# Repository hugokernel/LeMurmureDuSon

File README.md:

LeMurmureDuSon
==============

Projet de l'équipe nº1 du Museolab 2013 : Le murmure du son

Développement d'un post'it vocal sous la forme d'un cube

Caractéristiques
----------------

- 1 message enregistrable par face
- 1 texture différente par face
- Chaque message est limité à 6 secondes
- Possibilité d'enregistrement d'un nouveau message sur chaque face
- Charge par induction
- Détection de la face exposée vers le haut (accéléromètre)
- Le cube est translucide
- 1 vibreur
- Éclairage par 1 ou plusieurs led RGB
- Sur batterie
- Réalisable en impression 3D

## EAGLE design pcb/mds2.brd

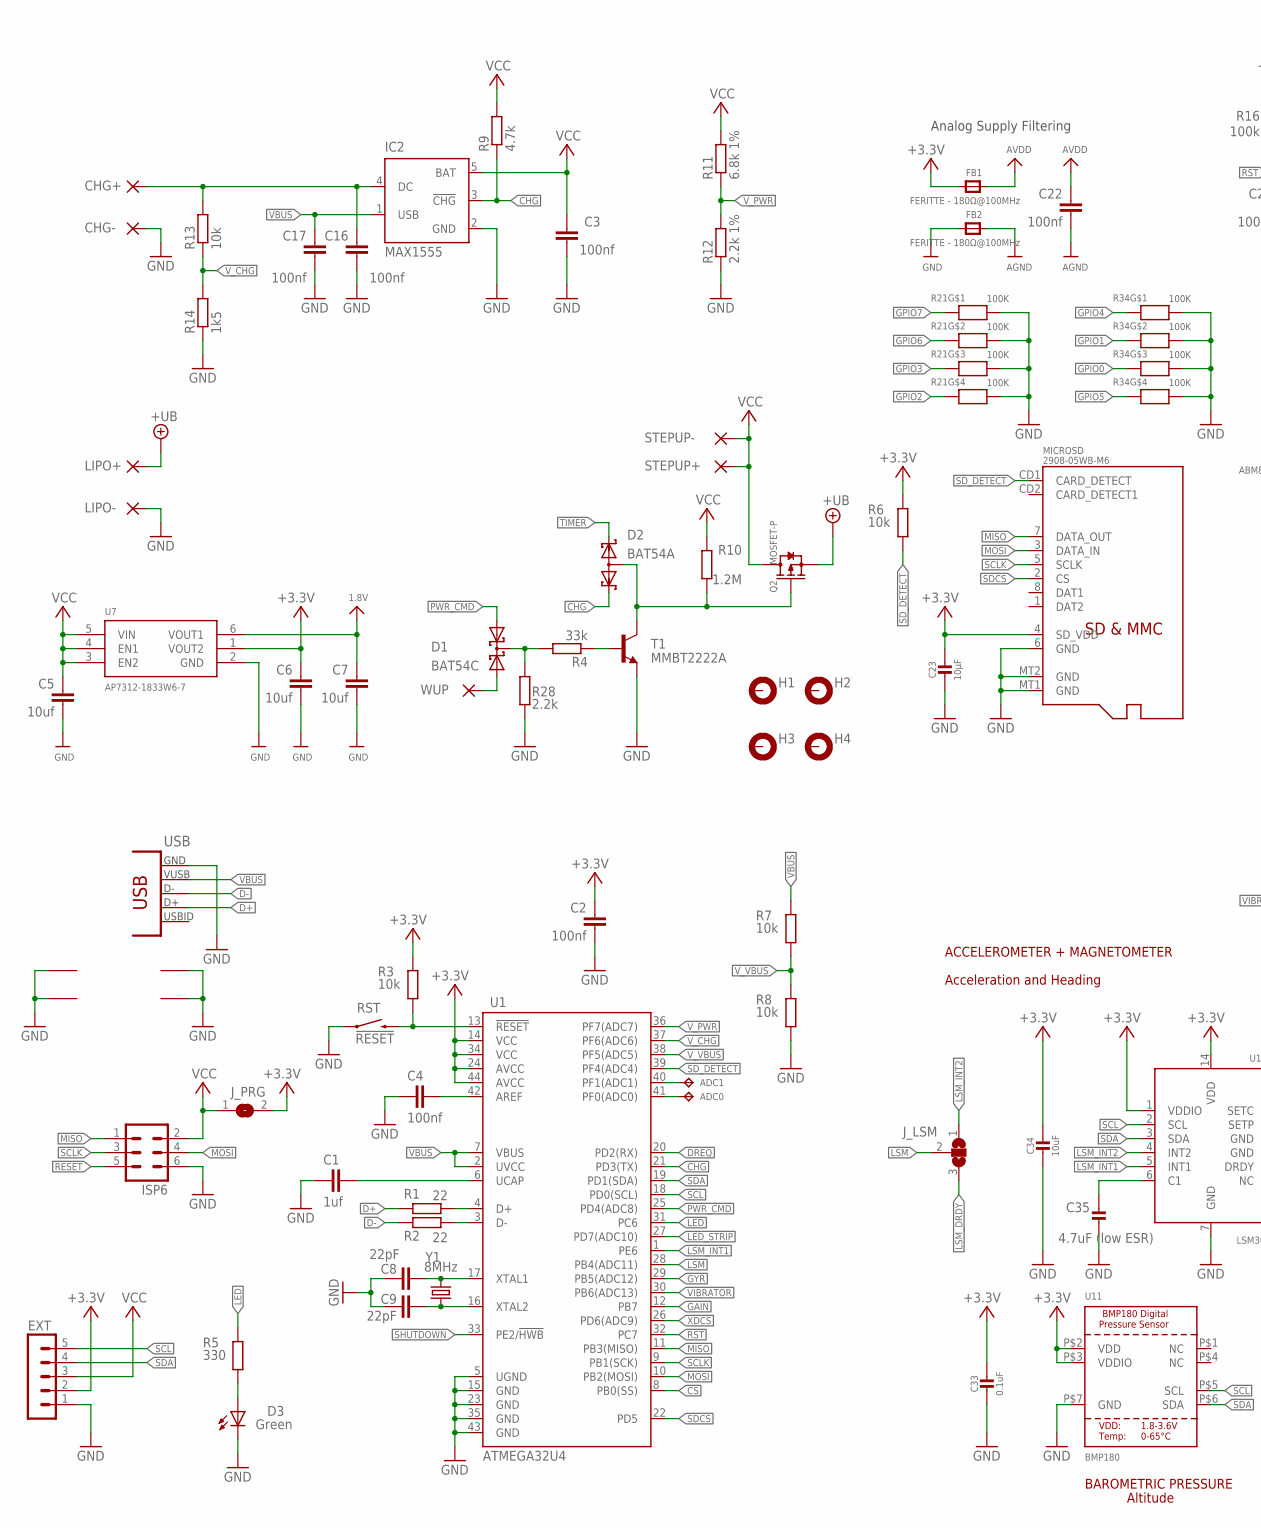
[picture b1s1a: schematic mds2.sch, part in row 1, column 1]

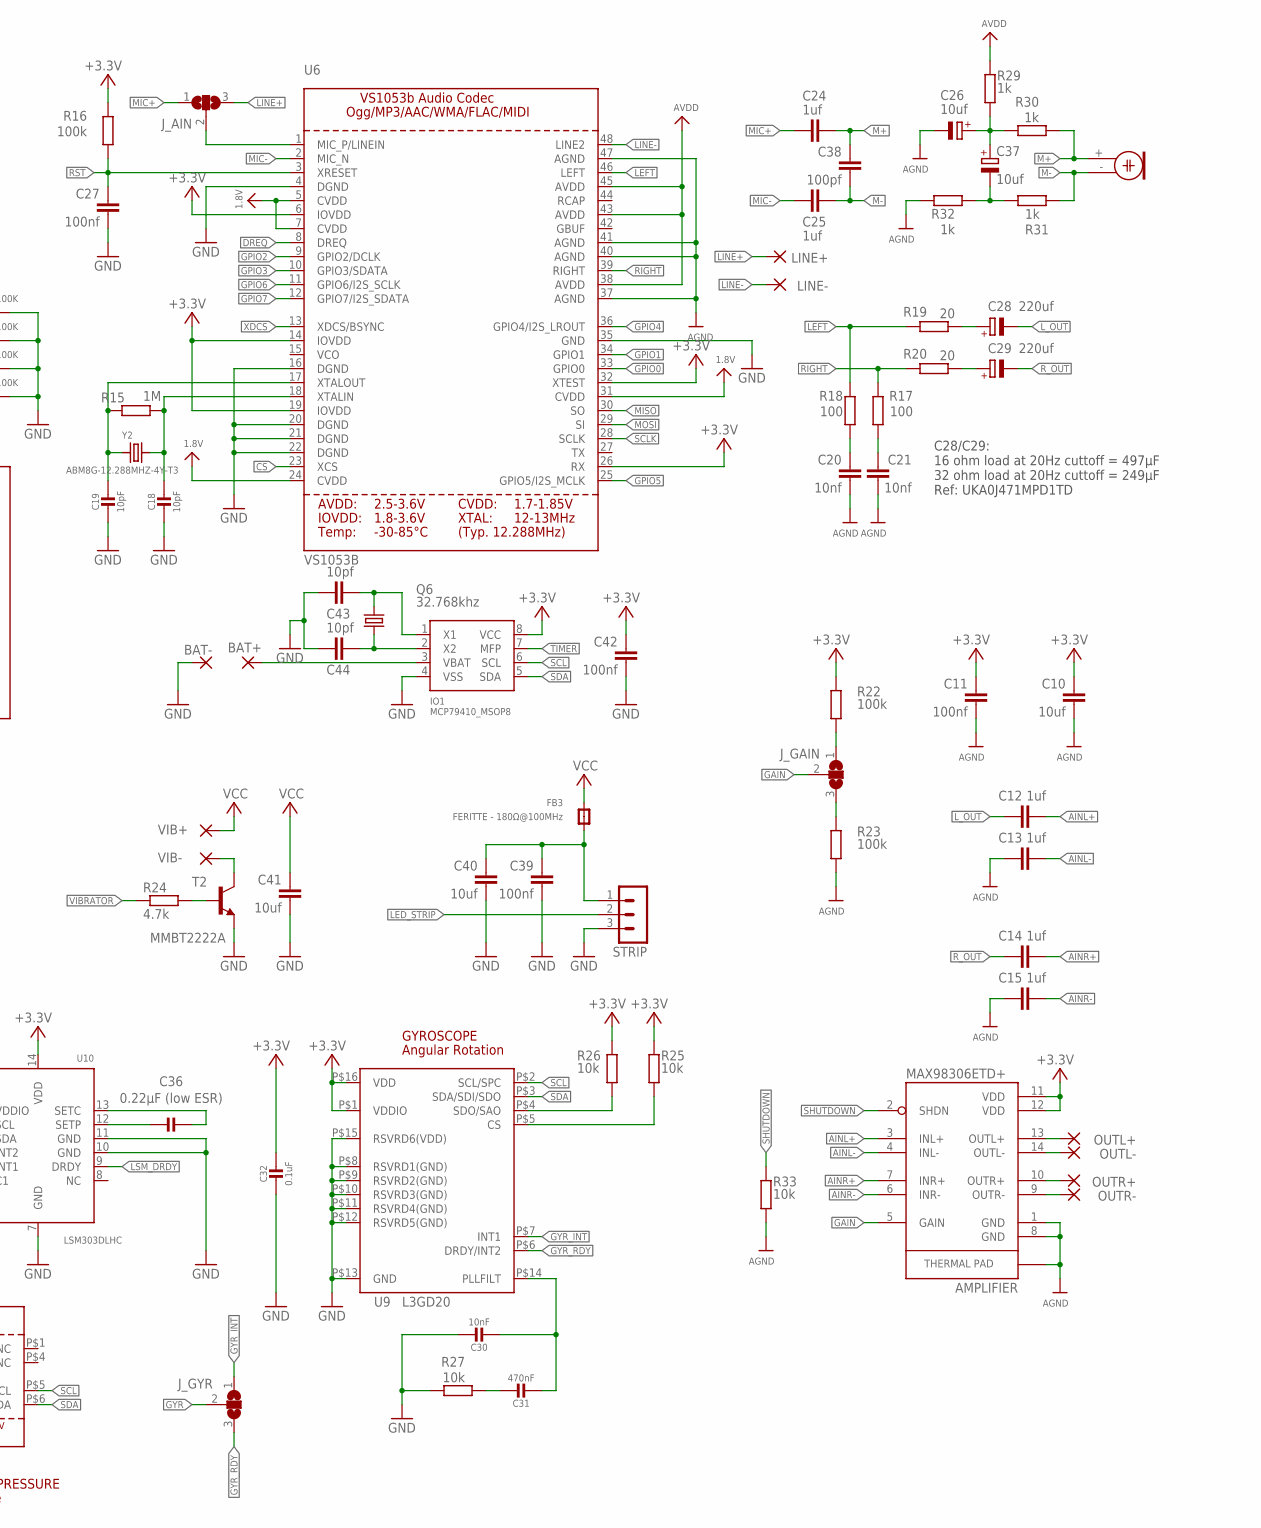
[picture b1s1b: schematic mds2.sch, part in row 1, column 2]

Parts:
ADC0, ADC1: TPB1,27; B1,27
AMPLIFIER: MAX98306ETD+; 14-TDFN
BAT+: 1,6/0,8
BAT-: 1,6/0,8
C1, C12, C13, C14, C15, C24, C25: 1uf; C0805
C2, C3, C4, C11, C16, C17, C22, C27, C39, C42: 100nf; C0805
C5, C6, C7, C10, C40, C41: 10uf; C0805
C8, C9: 22pF; 0402-CAP
C18, C19: 10pF; _0805MP
C20, C21: 10nf; C0805
C23: 10µF; _0805MP
C26, C37: 10uf; PANASONIC_C
C28, C29: 220uf; PANASONIC_D
C30: 10nF; _0805MP
C31: 470nF; _0805MP
C32, C33: 0.1uF; _0805MP
C34: 10uF; _0805MP
C35: 4.7uF (low ESR); _0805MP
C36: 0.22µF (low ESR); _0805MP
C38: 100pf; C0805
C43, C44: 10pf; C0805
CHG+: 2,15/1,0
CHG-: 2,15/1,0
D1: BAT54C; SOT23
D2: BAT54A; SOT23
D3: Green; LED-0603
EXT: MA05-1
FB1, FB2, FB3: FERITTE - 180Ω@100MHz; _0805MP
H1, H2, H3, H4: MOUNT-PAD-ROUND3.0; 3,0-PAD
IC2: MAX1555; SOT23-5L
IO1: MCP79410_MSOP8; MSOP8
ISP6: MA03-2
J_AIN: SJ2W; SJ_2
J_GAIN: SJ2W; SJ_2
J_GYR: SJ2W; SJ_2
J_LSM: SJ2W; SJ_2
J_PRG: SJ
LINE+: 1,6/0,8
LINE-: 1,6/0,8
LIPO+: 2,15/1,0
LIPO-: 2,15/1,0
MIC: ELECTRET_MICROPHON-TOM-1545P-R; TOM-1545P-R
MICROSD: 2908-05WB-M6; MICROSD
OUTL+: 2,15/1,0
OUTL-: 2,15/1,0
OUTR+: 2,15/1,0
OUTR-: 2,15/1,0
Q2: MOSFET-P; SOT23
Q6: 32.768khz; TC26H
R1, R2: 22; M0805
R3, R6, R7, R8, R13, R25, R26, R27, R33: 10k; M0805
R4: 33k; M0805
R5: 330; M0805
R9, R24: 4.7k; M0805
R10: 1.2M; M0805
R11: 6.8k 1%; M0805
R12: 2.2k 1%; M0805
R14: 1k5; M0805
R15: 1M; M0805
R16, R22, R23: 100k; M0805
R17, R18: 100; M0805
R19, R20: 20; M0805
R21, R34: 100K; RESPACK_4X0603
R28: 2.2k; M0805
R29, R30, R31, R32: 1k; M0805
RST: !RESET; TACTILE_SWITCH_SMD
STEPUP+: 2,15/1,0
STEPUP-: 2,15/1,0
STRIP: MA03-1
T1, T2: MMBT2222A; SOT23-BEC
U1: ATMEGA32U4; QFN-44-NOPAD
U6: VS1053B; LQFP48
U7: AP7312-1833W6-7; SOT23-6
U9: L3GD20; L3G4200D_LGA16L
U10: LSM303DLHC; LGA14
U11: BMP180; BMP180_EXTENDED
USB: CON-USB-F-MICRO-B; CONN_USB_MICRO-B
VIB+: 1,6/0,8
VIB-: 1,6/0,8
WUP: 1,6/0,8
Y1: 8MHz; CRYSTAL-SMD-5X3
Y2: ABM8G-12.288MHZ-4Y-T3; CRYSTAL_3.2X2.5

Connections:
1.8V: C7.2, U6.5 (CVDD), U6.7 (CVDD), U6.24 (CVDD), U6.31 (CVDD), U7.6 (VOUT1)
+3V3: AMPLIFIER.11 (VDD), AMPLIFIER.12 (VDD), C2.2, C6.2, C10.2, C11.2, C23.1, C32.1, C33.1, C34.1, C42.2, EXT.2, FB1.1, IO1.8 (VCC), J_PRG.2, MICROSD.4 (SD_VDD), R3.1, R6.1, R16.2, R22.2, R25.2, R26.2, U1.14 (VCC), U1.24 (AVCC), U1.34 (VCC), U1.44 (AVCC), U6.6 (IOVDD), U6.14 (IOVDD), U6.19 (IOVDD), U6.26 (RX), U6.32 (XTEST), U7.1 (VOUT2), U9.P$1 (VDDIO), U9.P$16 (VDD), U10.1 (VDDIO), U10.14 (VDD), U11.P$2 (VDD), U11.P$3 (VDDIO)
+UB: LIPO+.1, Q2.2 (S)
AGND: AMPLIFIER.1 (GND), AMPLIFIER.8 (GND), AMPLIFIER.15 (GND), C10.1, C11.1, C13.2, C15.2, C20.1, C21.1, C22.1, C26.-, FB2.2, R23.1, R32.1, R33.1, U6.37 (AGND), U6.40 (AGND), U6.41 (AGND), U6.47 (AGND)
AINL+: AMPLIFIER.3 (INL+), C12.1
AINL-: AMPLIFIER.4 (INL-), C13.1
AINR+: AMPLIFIER.7 (INR+), C14.1
AINR-: AMPLIFIER.6 (INR-), C15.1
AREF: C4.1, U1.42 (AREF)
AVDD: C22.2, FB1.2, R29.2, U6.38 (AVDD), U6.43 (AVDD), U6.45 (AVDD)
CHG: D2.2 (K2), IC2.3 (!CHG), R9.1, U1.21 (PD3(TX))
CS: U1.8 (PB0(SS)), U6.23 (XCS)
D+: R1.2, USB.P3 (D+)
D-: R2.2, USB.P2 (D-)
DREQ: U1.20 (PD2(RX)), U6.8 (DREQ)
GAIN: AMPLIFIER.5 (GAIN), J_GAIN.2, U1.12 (PB7)
GND: BAT-.1, C1.2, C2.1, C3.1, C4.2, C5.1, C6.1, C7.1, C8.2, C9.2, C16.1, C17.1, C18.2, C19.2, C23.2, C27.1, C30.1, C32.2, C33.2, C34.2, C35.2, C39.1, C40.1, C41.1, C42.1, C43.2, C44.2, CHG-.1, D3.C, EXT.1, FB2.1, IC2.2 (GND), IO1.4 (VSS), ISP6.6, LIPO-.1, MICROSD.6 (GND), MICROSD.MT1 (GND), MICROSD.MT2 (GND), R8.2, R12.1, R14.1, R21.5 (2), R21.6 (2), R21.7 (2), R21.8 (2), R27.1, R28.2, R34.5 (2), R34.6 (2), R34.7 (2), R34.8 (2), RST.1, STRIP.3, T1.E, T2.E, U1.5 (UGND), U1.15 (GND), U1.23 (GND), U1.35 (GND), U1.43 (GND), U6.4 (DGND), U6.16 (DGND), U6.20 (DGND), U6.21 (DGND), U6.22 (DGND), U6.35 (GND), U7.2 (GND), U9.P$8 (RSVRD1(GND)), U9.P$9 (RSVRD2(GND)), U9.P$10 (RSVRD3(GND)), U9.P$11 (RSVRD4(GND)), U9.P$12 (RSVRD5(GND)), U9.P$13 (GND), U9.P$15 (RSVRD6(VDD)), U10.7 (GND), U10.10 (GND), U10.11 (GND), U11.P$7 (GND), USB.BODY@1 (BODY), USB.BODY@2 (BODY)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
GPIO0: R34.3 (1), U6.33 (GPIO0)
GPIO1: R34.2 (1), U6.34 (GPIO1)
GPIO2: R21.4 (1), U6.9 (GPIO2/DCLK)
GPIO3: R21.3 (1), U6.10 (GPIO3/SDATA)
GPIO4: R34.1, U6.36 (GPIO4/I2S_LROUT)
GPIO5: R34.4 (1), U6.25 (GPIO5/I2S_MCLK)
GPIO6: R21.2 (1), U6.11 (GPIO6/I2S_SCLK)
GPIO7: R21.1, U6.12 (GPIO7/I2S_SDATA)
GYR: J_GYR.2, U1.29 (PB5(ADC12))
GYR_INT: J_GYR.1, U9.P$7 (INT1)
GYR_RDY: J_GYR.3, U9.P$6 (DRDY/INT2)
LED: R5.1, U1.31 (PC6)
LED_STRIP: STRIP.2, U1.27 (PD7(ADC10))
LEFT: R17.2, R19.2, U6.46 (LEFT)
LEFT_FILTERED: C28.+, R19.1
LINE+: J_AIN.3, LINE+.1
LINE-: LINE-.1, U6.48 (LINE2)
LSM: J_LSM.2, U1.28 (PB4(ADC11))
LSM_DRDY: J_LSM.3, U10.9 (DRDY)
LSM_INT1: U1.1 (PE6), U10.5 (INT1)
LSM_INT2: J_LSM.1, U10.4 (INT2)
L_OUT: C12.2, C28.-
M+: C24.1, C38.2, MIC.+ (1), R30.2
M-: C25.1, C38.1, MIC.- (2), R31.1
MIC+: C24.2, J_AIN.1
MIC-: C25.2, U6.2 (MIC_N)
MISO: ISP6.1, MICROSD.7 (DATA_OUT), U1.11 (PB3(MISO)), U6.30 (SO)
MOSI: ISP6.4, MICROSD.3 (DATA_IN), U1.10 (PB2(MOSI)), U6.29 (SI)
unnamed: C9.1, U1.16 (XTAL2), Y1.1
unnamed: R1.1, U1.4 (D+)
unnamed: C16.2, CHG+.1, IC2.4 (DC), R13.2
unnamed: C8.1, U1.17 (XTAL1), Y1.3 (2)
unnamed: C1.1, U1.6 (UCAP)
unnamed: C39.2, C40.2, FB3.1, STRIP.1
unnamed: R2.1, U1.3 (D-)
unnamed: D3.A, R5.2
unnamed: R4.1, T1.B
unnamed: D2.3 (AA), Q2.1 (G), R10.1, T1.C
unnamed: D1.3 (CC), R4.2, R28.1
unnamed: D1.2 (A2), WUP.1
unnamed: R24.2, T2.B
unnamed: T2.C, VIB-.1
unnamed: ADC1.TP, U1.40 (PF1(ADC1))
unnamed: J_AIN.2, U6.1 (MIC_P/LINEIN)
unnamed: AMPLIFIER.14 (OUTL-), OUTL-.1
unnamed: J_GAIN.1, R22.1
unnamed: AMPLIFIER.13 (OUTL+), OUTL+.1
unnamed: C37.-, R31.2, R32.2
unnamed: ADC0.TP, U1.41 (PF0(ADC0))
unnamed: C44.1, IO1.2 (X2), Q6.1
unnamed: C26.+, C37.+, R29.1, R30.1
unnamed: AMPLIFIER.10 (OUTR+), OUTR+.1
unnamed: AMPLIFIER.9 (OUTR-), OUTR-.1
unnamed: J_GAIN.3, R23.2
unnamed: C43.1, IO1.1 (X1), Q6.2
unnamed: C19.1, R15.2, U6.17 (XTALOUT), Y2.1
unnamed: C18.1, R15.1, U6.18 (XTALIN), Y2.2
unnamed: C20.2, R17.1
unnamed: C21.2, R18.1
unnamed: BAT+.1, IO1.3 (VBAT)
unnamed: R25.1, U9.P$5 (CS)
unnamed: R26.1, U9.P$4 (SDO/SAO)
unnamed: C31.1, R27.2
unnamed: C30.2, C31.2, U9.P$14 (PLLFILT)
unnamed: C35.1, U10.6 (C1)
unnamed: C36.1, U10.12 (SETP)
unnamed: C36.2, U10.13 (SETC)
PWR_CMD: D1.1 (A1), U1.25 (PD4(ADC8))
RESET: ISP6.5, R3.2, RST.3 (2), U1.13 (!RESET)
RIGHT: R18.2, R20.2, U6.39 (RIGHT)
RIGHT_FILTERED: C29.+, R20.1
RST: C27.2, R16.1, U1.32 (PC7), U6.3 (XRESET)
R_OUT: C14.2, C29.-
SCL: EXT.5, IO1.6 (SCL), U1.18 (PD0(SCL)), U9.P$2 (SCL/SPC), U10.2 (SCL), U11.P$5 (SCL)
SCLK: ISP6.3, MICROSD.5 (SCLK), U1.9 (PB1(SCK)), U6.28 (SCLK)
SDA: EXT.4, IO1.5 (SDA), U1.19 (PD1(SDA)), U9.P$3 (SDA/SDI/SDO), U10.3 (SDA), U11.P$6 (SDA)
SDCS: MICROSD.2 (CS), U1.22 (PD5)
SD_DETECT: MICROSD.CD1 (CARD_DETECT), R6.2, U1.39 (PF4(ADC4))
SHUTDOWN: AMPLIFIER.2 (SHDN), R33.2, U1.33 (PE2/!HWB)
TIMER: D2.1 (K1), IO1.7 (MFP)
VBUS: C17.2, IC2.1 (USB), R7.1, U1.2 (UVCC), U1.7 (VBUS), USB.P1 (VUSB)
VCC: C3.2, C5.2, C41.2, EXT.3, FB3.2, IC2.5 (BAT), ISP6.2, J_PRG.1, Q2.3 (D), R9.2, R10.2, R11.2, STEPUP+.1, STEPUP-.1, U7.3 (EN2), U7.4 (EN1), U7.5 (VIN), VIB+.1
VIBRATOR: R24.1, U1.30 (PB6(ADC13))
V_CHG: R13.1, R14.2, U1.37 (PF6(ADC6))
V_PWR: R11.1, R12.2, U1.36 (PF7(ADC7))
V_VBUS: R7.2, R8.1, U1.38 (PF5(ADC5))
XDCS: U1.26 (PD6(ADC9)), U6.13 (XDCS/BSYNC)

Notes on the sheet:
Analog Supply Filtering
C28/C29: 16 ohm load at 20Hz cuttoff = 497µF 32 ohm load at 20Hz cuttoff = 249µF Ref: UKA0J471MPD1TD
GYROSCOPE
Angular Rotation
ACCELEROMETER + MAGNETOMETER
Acceleration and Heading
BAROMETRIC PRESSURE
Altitude

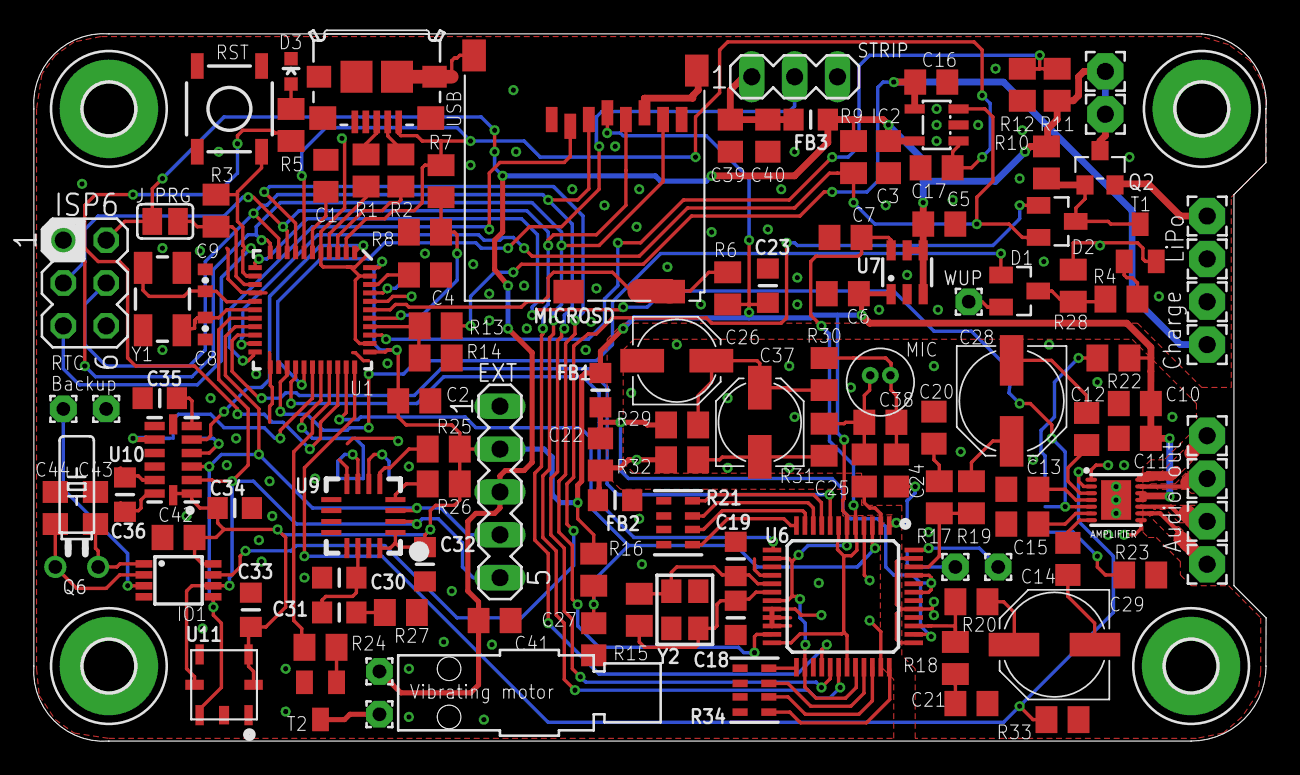
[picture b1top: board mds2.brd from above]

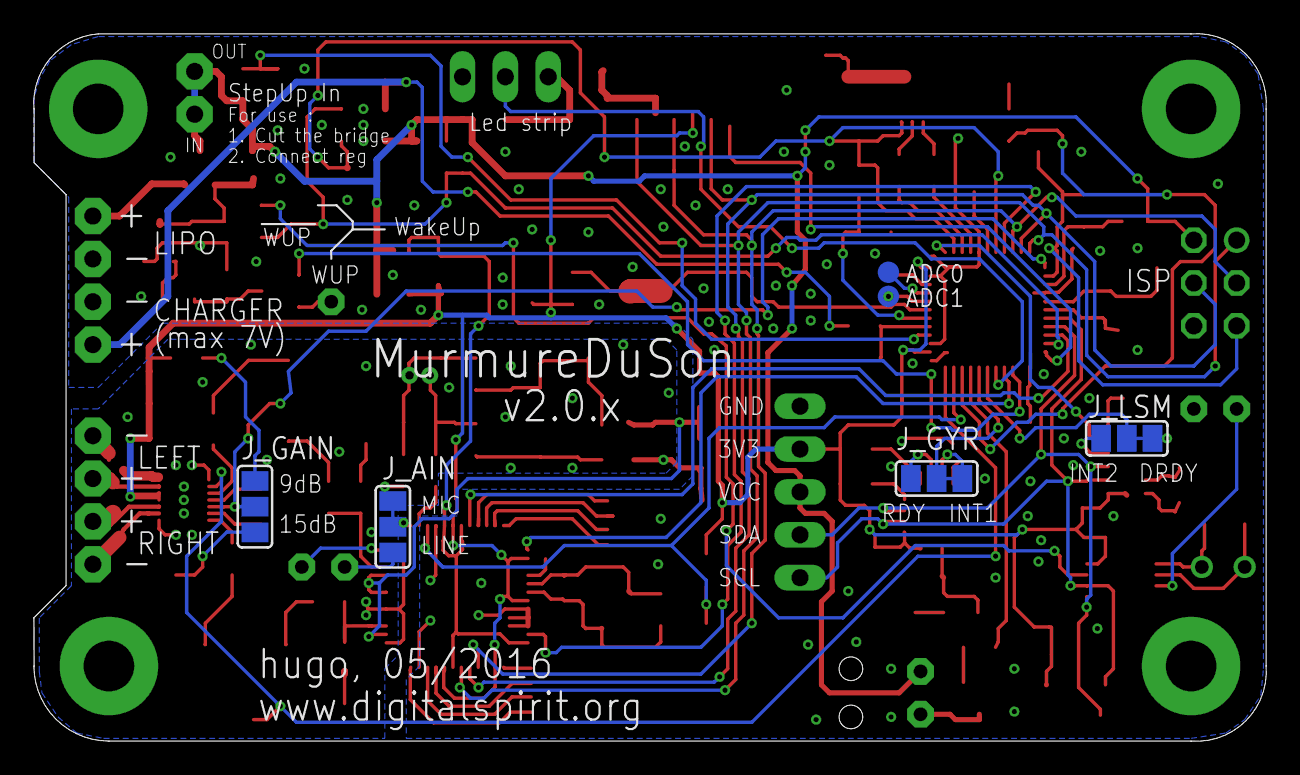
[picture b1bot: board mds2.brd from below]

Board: 2 copper layers, 73.0 x 41.9 mm, 134 parts (6 on the bottom side), 104 nets.

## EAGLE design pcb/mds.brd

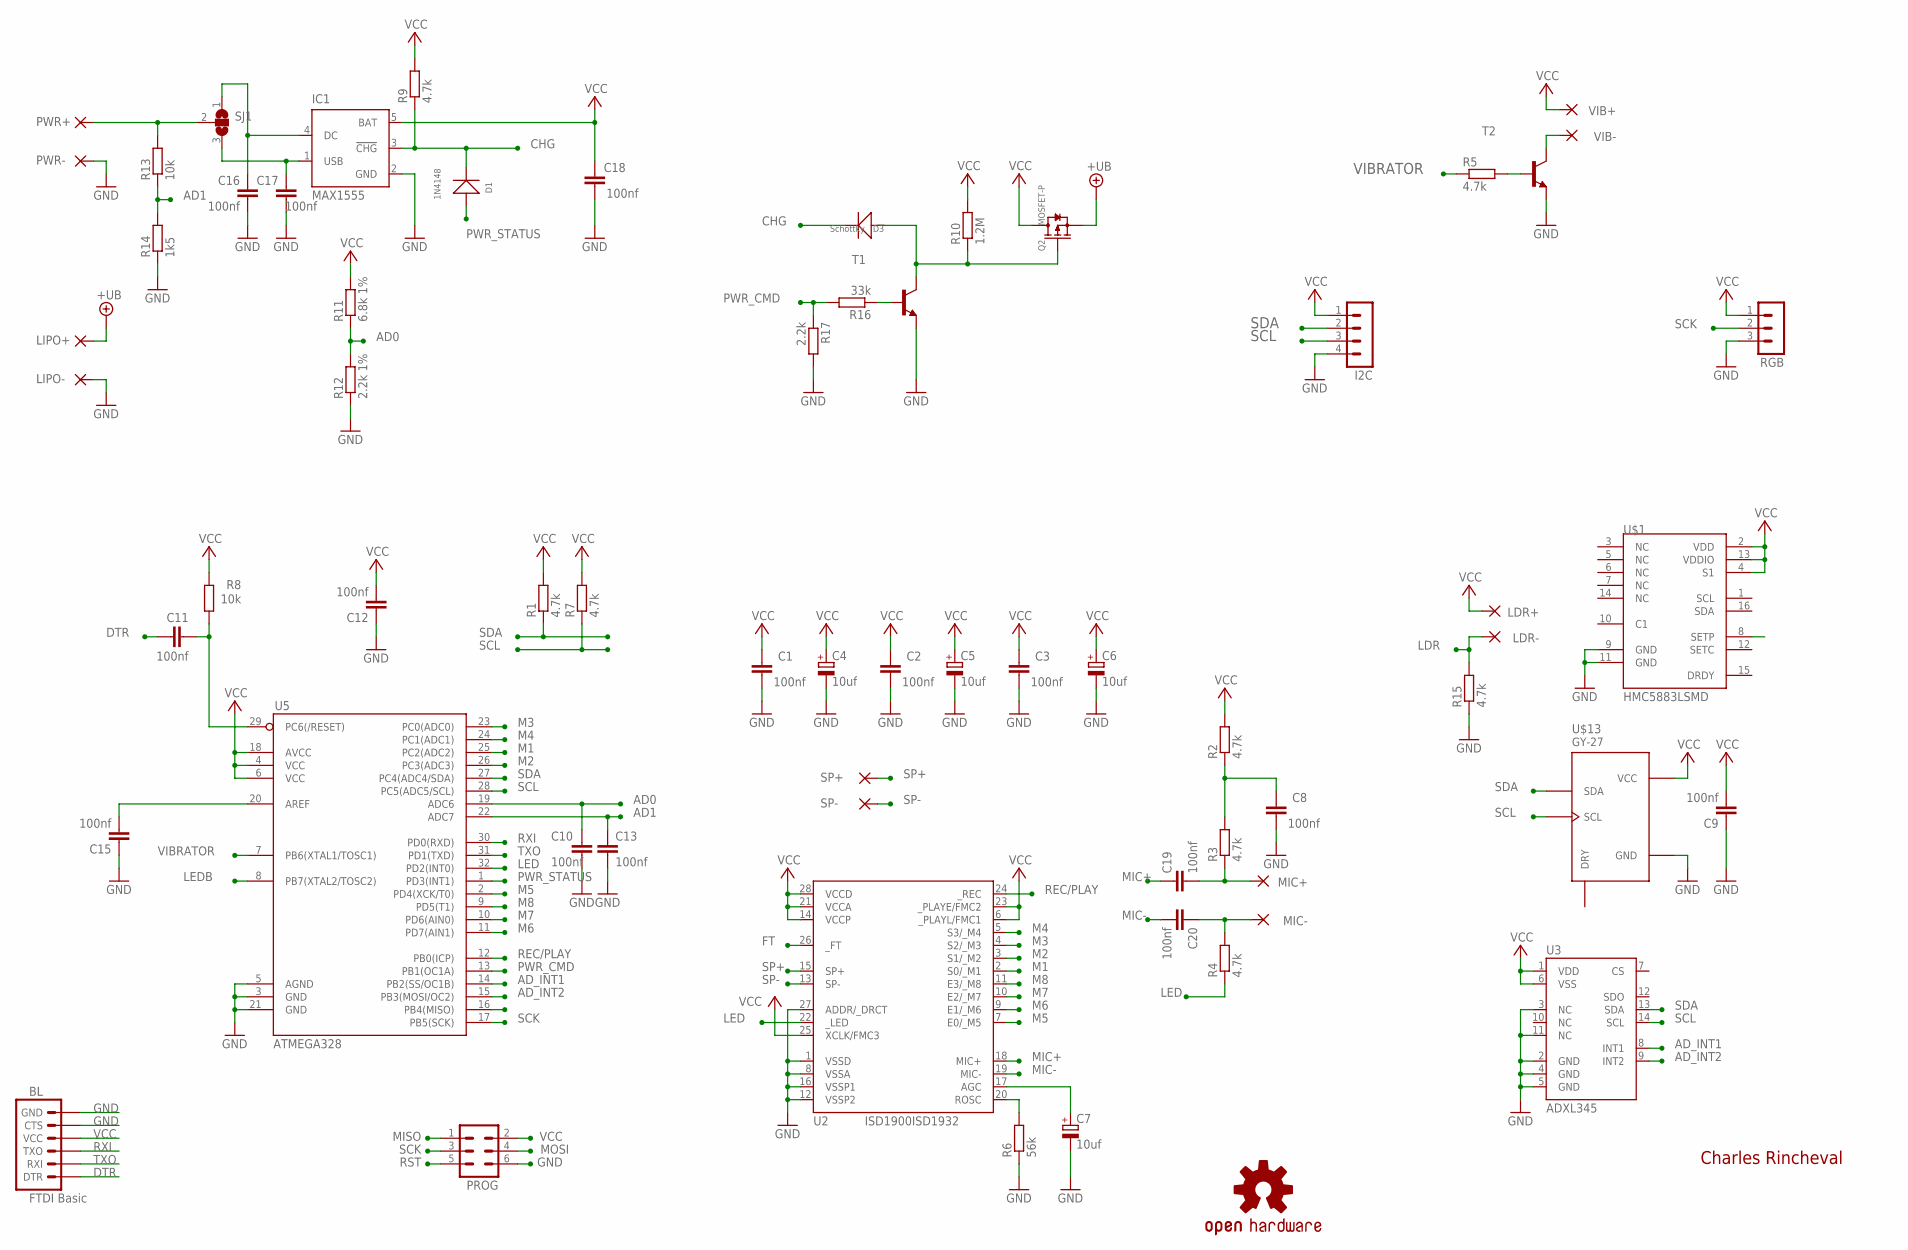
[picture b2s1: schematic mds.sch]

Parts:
BL: FTDI Basic; 1X06
C1, C2, C3, C8, C9, C10, C11, C12, C13, C15, C16, C17, C18, C19, C20: 100nf; C0805
C4, C5, C6, C7: 10uf; CT3528
D1: 1N4148; LL-34
D3: Schottky; LL-34
I2C: MA04-1
IC1: MAX1555; SOT23-5L
LDR+: 1,6/0,8
LDR-: 1,6/0,8
LIPO+: 1,6/0,8
LIPO-: 1,6/0,8
MIC+: 1,6/0,8
MIC-: 1,6/0,8
PROG: MA03-2
PWR+: 1,6/0,8
PWR-: 1,6/0,8
Q2: MOSFET-P; SOT23
R1, R2, R3, R4, R5, R7, R9, R15: 4.7k; M0805
R6: 56k; M0805
R8, R13: 10k; M0805
R10: 1.2M; M0805
R11: 6.8k 1%; M0805
R12: 2.2k 1%; M0805
R14: 1k5; M0805
R16: 33k; M0805
R17: 2.2k; M0805
RGB: MA03-1
SJ1: SJ2W; SJ_2
SP+: 1,6/0,8
SP-: 1,6/0,8
T1, T2: MMBT2222ALT1-NPN-SOT23-BEC; SOT23-BEC
U2: ISD1900ISD1932; SO-28W
U3: ADXL345; LGA14
U5: ATMEGA328; TQFP32-08
U$1: HMC5883LSMD; 16LPCC
U$13: GY-27
U$14: OSHW-LOGOS; OSHW-LOGO-S
VIB+: 1,6/0,8
VIB-: 1,6/0,8

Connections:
+UB: LIPO+.1, Q2.2 (S)
AD0: C10.1, R11.1, R12.2, U5.19 (ADC6)
AD1: C13.1, R13.1, R14.2, U5.22 (ADC7)
AD_INT1: U3.8 (INT1), U5.14 (PB2(SS/OC1B))
AD_INT2: U3.9 (INT2), U5.15 (PB3(MOSI/OC2))
AGC: C7.+, U2.17 (AGC)
AREF: C15.2, U5.20 (AREF)
CHG: D1.C (-), D3.C (-), IC1.3 (!CHG), R9.1
DTR: BL.1 (DTR), C11.1
FT: U2.26 (_FT)
GND: BL.5 (CTS), BL.6 (GND), C1.1, C2.1, C3.1, C4.-, C5.-, C6.-, C7.-, C8.1, C9.1, C10.2, C12.1, C13.2, C15.1, C16.1, C17.1, C18.1, I2C.4, IC1.2 (GND), LIPO-.1, PROG.6, PWR-.1, R6.1, R12.1, R14.1, R15.1, R17.2, RGB.3, T1.E, T2.E, U2.1 (VSSD), U2.8 (VSSA), U2.12 (VSSP2), U2.16 (VSSP1), U2.27 (ADDR/_DRCT), U3.2 (GND), U3.3 (NC), U3.4 (GND), U3.5 (GND), U3.11 (NC), U5.3 (GND), U5.5 (AGND), U5.21 (GND), U$1.9 (GND), U$1.11 (GND), U$13.GND
LDR: LDR-.1, R15.2
LED: R4.1, U2.22 (_LED), U5.32 (PD2(INT0))
LEDB: U5.8 (PB7(XTAL2/TOSC2))
M1: U2.2 (S0/_M1), U5.25 (PC2(ADC2))
M2: U2.3 (S1/_M2), U5.26 (PC3(ADC3))
M3: U2.4 (S2/_M3), U5.23 (PC0(ADC0))
M4: U2.5 (S3/_M4), U5.24 (PC1(ADC1))
M5: U2.7 (E0/_M5), U5.2 (PD4(XCK/T0))
M6: U2.9 (E1/_M6), U5.11 (PD7(AIN1))
M7: U2.10 (E2/_M7), U5.10 (PD6(AIN0))
M8: U2.11 (E3/_M8), U5.9 (PD5(T1))
MIC+: C19.1, U2.18 (MIC+)
MIC-: C20.2, U2.19 (MIC-)
MISO: PROG.1
MOSI: PROG.4
unnamed: R6.2, U2.20 (ROSC)
unnamed: C19.2, MIC+.1, R3.1
unnamed: C20.1, MIC-.1, R4.2
unnamed: R16.1, T1.B
unnamed: R5.2, T2.B
unnamed: C8.2, R2.1, R3.2
unnamed: T2.C, VIB-.1
unnamed: PWR+.1, R13.2, SJ1.2
unnamed: Q2.1 (G), R10.1, T1.C
unnamed: C17.2, IC1.1 (USB), SJ1.3
unnamed: C16.2, IC1.4 (DC), SJ1.1
PWR_CMD: R16.2, R17.1, U5.13 (PB1(OC1A))
PWR_STATUS: D1.A (+), U5.1 (PD3(INT1))
REC/PLAY: U2.24 (_REC), U5.12 (PB0(ICP))
RST: C11.2, PROG.5, R8.1, U5.29 (PC6(/RESET))
RXI: BL.3 (TXO), U5.30 (PD0(RXD))
SCK: PROG.3, RGB.2, U5.17 (PB5(SCK))
SCL: I2C.3, R7.1, U3.14 (SCL), U5.28 (PC5(ADC5/SCL)), U$13.SCL
SDA: I2C.2, R1.1, U3.13 (SDA), U5.27 (PC4(ADC4/SDA)), U$13.SDA
SP+: SP+.1, U2.15 (SP+)
SP-: SP-.1, U2.13 (SP-)
TXO: BL.2 (RXI), U5.31 (PD1(TXD))
VCC: BL.4 (VCC), C1.2, C2.2, C3.2, C4.+, C5.+, C6.+, C9.2, C12.2, C18.2, I2C.1, IC1.5 (BAT), LDR+.1, PROG.2, Q2.3 (D), R1.2, R2.2, R7.2, R8.2, R9.2, R10.2, R11.2, RGB.1, U2.6 (_PLAYL/FMC1), U2.14 (VCCP), U2.21 (VCCA), U2.23 (_PLAYE/FMC2), U2.25 (XCLK/FMC3), U2.28 (VCCD), U3.1 (VDD), U3.6 (VSS), U5.4 (VCC), U5.6 (VCC), U5.18 (AVCC), U$1.2 (VDD), U$1.4 (S1), U$1.13 (VDDIO), U$13.VCC, VIB+.1
VIBRATOR: R5.1, U5.7 (PB6(XTAL1/TOSC1))

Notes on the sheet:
Charles Rincheval

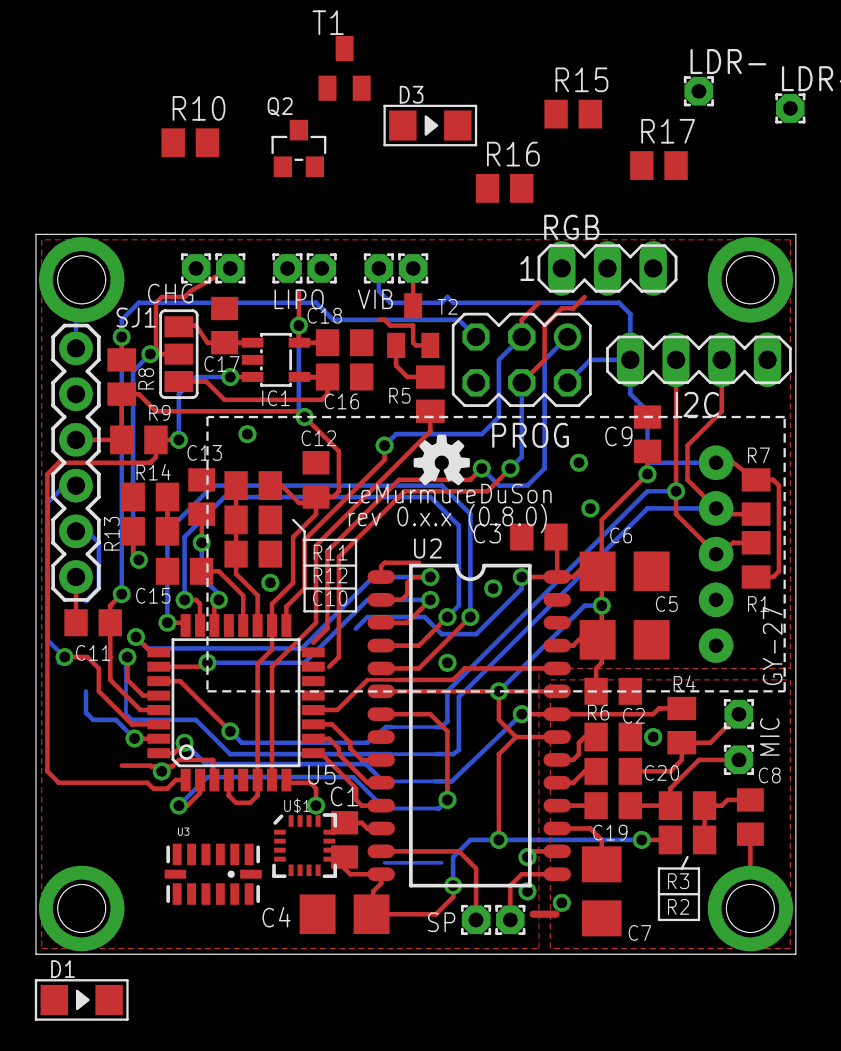
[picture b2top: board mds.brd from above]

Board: 2 copper layers, 42.2 x 40.0 mm, 65 parts (0 on the bottom side), 46 nets.

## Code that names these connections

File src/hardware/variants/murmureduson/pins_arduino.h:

/*
  pins_arduino.h - Pin definition functions for Arduino
  Part of Arduino - http://www.arduino.cc/

  Copyright (c) 2007 David A. Mellis

  This library is free software; you can redistribute it and/or
  modify it under the terms of the GNU Lesser General Public
  License as published by the Free Software Foundation; either
  version 2.1 of the License, or (at your option) any later version.

  This library is distributed in the hope that it will be useful,
  but WITHOUT ANY WARRANTY; without even the implied warranty of
  MERCHANTABILITY or FITNESS FOR A PARTICULAR PURPOSE.  See the GNU
  Lesser General Public License for more details.

  You should have received a copy of the GNU Lesser General
  Public License along with this library; if not, write to the
  Free Software Foundation, Inc., 59 Temple Place, Suite 330,
  Boston, MA  02111-1307  USA

  $Id: wiring.h 249 2007-02-03 16:52:51Z mellis $
*/

#ifndef Pins_Arduino_h
#define Pins_Arduino_h

#include <avr/pgmspace.h>

// Workaround for wrong definitions in "iom32u4.h".
// This should be fixed in the AVR toolchain.
#undef UHCON
#undef UHINT
#undef UHIEN
#undef UHADDR
#undef UHFNUM
#undef UHFNUML
#undef UHFNUMH
#undef UHFLEN
#undef UPINRQX
#undef UPINTX
#undef UPNUM
#undef UPRST
#undef UPCONX
#undef UPCFG0X
#undef UPCFG1X
#undef UPSTAX
#undef UPCFG2X
#undef UPIENX
#undef UPDATX
#undef TCCR2A
#undef WGM20
#undef WGM21
#undef COM2B0
#undef COM2B1
#undef COM2A0
#undef COM2A1
#undef TCCR2B
#undef CS20
#undef CS21
#undef CS22
#undef WGM22
#undef FOC2B
#undef FOC2A
#undef TCNT2
#undef TCNT2_0
#undef TCNT2_1
#undef TCNT2_2
#undef TCNT2_3
#undef TCNT2_4
#undef TCNT2_5
#undef TCNT2_6
#undef TCNT2_7
#undef OCR2A
#undef OCR2_0
#undef OCR2_1
#undef OCR2_2
#undef OCR2_3
#undef OCR2_4
#undef OCR2_5
#undef OCR2_6
#undef OCR2_7
#undef OCR2B
#undef OCR2_0
#undef OCR2_1
#undef OCR2_2
#undef OCR2_3
#undef OCR2_4
#undef OCR2_5
#undef OCR2_6
#undef OCR2_7

#define NUM_DIGITAL_PINS  30
#define NUM_ANALOG_INPUTS 12

#define TX_RX_LED_INIT	; //DDRD |= (1<<5), DDRB |= (1<<0)
#define TXLED0			; //PORTD |= (1<<5)
#define TXLED1			; //PORTD &= ~(1<<5)
#define RXLED0			; //PORTB |= (1<<0)
#define RXLED1			; //PORTB &= ~(1<<0)

static const uint8_t SDA = 2;
static const uint8_t SCL = 3;

// Map SPI port to 'new' pins D14..D17
static const uint8_t SS   = 17;
static const uint8_t MOSI = 16;
static const uint8_t MISO = 14;
static const uint8_t SCK  = 15;

// Mapping of analog pins as digital I/O
// A6-A11 share with digital pins
static const uint8_t A0 = 18;
static const uint8_t A1 = 19;
static const uint8_t A2 = 20;
static const uint8_t A3 = 21;
static const uint8_t A4 = 22;
static const uint8_t A5 = 23;
static const uint8_t A6 = 24;	// D4
static const uint8_t A7 = 25;	// D6
static const uint8_t A8 = 26;	// D8
static const uint8_t A9 = 27;	// D9
static const uint8_t A10 = 28;	// D10
static const uint8_t A11 = 29;	// D12

#define digitalPinToPCICR(p)    ((((p) >= 8 && (p) <= 11) || ((p) >= 14 && (p) <= 17) || ((p) >= A8 && (p) <= A10)) ? (&PCICR) : ((uint8_t *)0))
#define digitalPinToPCICRbit(p) 0
#define digitalPinToPCMSK(p)    ((((p) >= 8 && (p) <= 11) || ((p) >= 14 && (p) <= 17) || ((p) >= A8 && (p) <= A10)) ? (&PCMSK0) : ((uint8_t *)0))
#define digitalPinToPCMSKbit(p) ( ((p) >= 8 && (p) <= 11) ? (p) - 4 : ((p) == 14 ? 3 : ((p) == 15 ? 1 : ((p) == 16 ? 2 : ((p) == 17 ? 0 : (p - A8 + 4))))))

//	__AVR_ATmega32U4__ has an unusual mapping of pins to channels
extern const uint8_t PROGMEM analog_pin_to_channel_PGM[];
#define analogPinToChannel(P)  ( pgm_read_byte( analog_pin_to_channel_PGM + (P) ) )

#ifdef ARDUINO_MAIN

// On the Arduino board, digital pins are also used
// for the analog output (software PWM).  Analog input
// pins are a separate set.

// ATMEL ATMEGA32U4 / ARDUINO LEONARDO
//
// D0				PD2					RXD1/INT2
// D1				PD3					TXD1/INT3
// D2				PD1		SDA			SDA/INT1
// D3#				PD0		PWM8/SCL	OC0B/SCL/INT0
// D4		A6		PD4					ADC8
// D5#				PC6		???			OC3A/#OC4A
// D6#		A7		PD7		FastPWM		#OC4D/ADC10
// D7				PE6					INT6/AIN0
//
// D8		A8		PB4					ADC11/PCINT4
// D9#		A9		PB5		PWM16		OC1A/#OC4B/ADC12/PCINT5
// D10#		A10		PB6		PWM16		OC1B/0c4B/ADC13/PCINT6
// D11#				PB7		PWM8/16		0C0A/OC1C/#RTS/PCINT7
// D12		A11		PD6					T1/#OC4D/ADC9
// D13#				PC7		PWM10		CLK0/OC4A
//
// A0		D18		PF7					ADC7
// A1		D19		PF6					ADC6
// A2		D20 	PF5					ADC5
// A3		D21 	PF4					ADC4
// A4		D22		PF1					ADC1
// A5		D23 	PF0					ADC0
//
// New pins D14..D17 to map SPI port to digital pins
//
// MISO		D14		PB3					MISO,PCINT3
// SCK		D15		PB1					SCK,PCINT1
// MOSI		D16		PB2					MOSI,PCINT2
// SS		D17		PB0					RXLED,SS/PCINT0
//
// TXLED			PD5
// RXLED		    PB0
// HWB				PE2					HWB

// these arrays map port names (e.g. port B) to the
// appropriate addresses for various functions (e.g. reading
// and writing)
const uint16_t PROGMEM port_to_mode_PGM[] = {
	NOT_A_PORT,
	NOT_A_PORT,
	(uint16_t) &DDRB,
	(uint16_t) &DDRC,
	(uint16_t) &DDRD,
	(uint16_t) &DDRE,
	(uint16_t) &DDRF,
};

const uint16_t PROGMEM port_to_output_PGM[] = {
	NOT_A_PORT,
	NOT_A_PORT,
	(uint16_t) &PORTB,
	(uint16_t) &PORTC,
	(uint16_t) &PORTD,
	(uint16_t) &PORTE,
	(uint16_t) &PORTF,
};

const uint16_t PROGMEM port_to_input_PGM[] = {
	NOT_A_PORT,
	NOT_A_PORT,
	(uint16_t) &PINB,
	(uint16_t) &PINC,
	(uint16_t) &PIND,
	(uint16_t) &PINE,
	(uint16_t) &PINF,
};

const uint8_t PROGMEM digital_pin_to_port_PGM[] = {
	PD, // D0 - PD2
	PD,	// D1 - PD3
	PD, // D2 - PD1
	PD,	// D3 - PD0
	PD,	// D4 - PD4
	PC, // D5 - PC6
	PD, // D6 - PD7
	PE, // D7 - PE6
	
	PB, // D8 - PB4
	PB,	// D9 - PB5
	PB, // D10 - PB6
	PB,	// D11 - PB7
	PD, // D12 - PD6
	PC, // D13 - PC7
	
	PB,	// D14 - MISO - PB3
	PB,	// D15 - SCK - PB1
	PB,	// D16 - MOSI - PB2
	PB,	// D17 - SS - PB0
	
	PF,	// D18 - A0 - PF7
	PF, // D19 - A1 - PF6
	PF, // D20 - A2 - PF5
	PF, // D21 - A3 - PF4
	PF, // D22 - A4 - PF1
	PF, // D23 - A5 - PF0
	
	PD, // D24 / D4 - A6 - PD4
	PD, // D25 / D6 - A7 - PD7
	PB, // D26 / D8 - A8 - PB4
	PB, // D27 / D9 - A9 - PB5
	PB, // D28 / D10 - A10 - PB6
	PD, // D29 / D12 - A11 - PD6
};

const uint8_t PROGMEM digital_pin_to_bit_mask_PGM[] = {
	_BV(2), // D0 - PD2
	_BV(3),	// D1 - PD3
	_BV(1), // D2 - PD1
	_BV(0),	// D3 - PD0
	_BV(4),	// D4 - PD4
	_BV(6), // D5 - PC6
	_BV(7), // D6 - PD7
	_BV(6), // D7 - PE6
	
	_BV(4), // D8 - PB4
	_BV(5),	// D9 - PB5
	_BV(6), // D10 - PB6
	_BV(7),	// D11 - PB7
	_BV(6), // D12 - PD6
	_BV(7), // D13 - PC7
	
	_BV(3),	// D14 - MISO - PB3
	_BV(1),	// D15 - SCK - PB1
	_BV(2),	// D16 - MOSI - PB2
	_BV(0),	// D17 - SS - PB0
	
	_BV(7),	// D18 - A0 - PF7
	_BV(6), // D19 - A1 - PF6
	_BV(5), // D20 - A2 - PF5
	_BV(4), // D21 - A3 - PF4
	_BV(1), // D22 - A4 - PF1
	_BV(0), // D23 - A5 - PF0
	
	_BV(4), // D24 / D4 - A6 - PD4
	_BV(7), // D25 / D6 - A7 - PD7
	_BV(4), // D26 / D8 - A8 - PB4
	_BV(5), // D27 / D9 - A9 - PB5
	_BV(6), // D28 / D10 - A10 - PB6
	_BV(6), // D29 / D12 - A11 - PD6
};

const uint8_t PROGMEM digital_pin_to_timer_PGM[] = {
	NOT_ON_TIMER,	
	NOT_ON_TIMER,
	NOT_ON_TIMER,
	TIMER0B,		/* 3 */
	NOT_ON_TIMER,
	TIMER3A,		/* 5 */
	TIMER4D,		/* 6 */
	NOT_ON_TIMER,	
	
	NOT_ON_TIMER,	
	TIMER1A,		/* 9 */
	TIMER1B,		/* 10 */
	TIMER0A,		/* 11 */
	
	NOT_ON_TIMER,	
	TIMER4A,		/* 13 */
	
	NOT_ON_TIMER,	
	NOT_ON_TIMER,
	NOT_ON_TIMER,
	NOT_ON_TIMER,
	NOT_ON_TIMER,
	NOT_ON_TIMER,

	NOT_ON_TIMER,
	NOT_ON_TIMER,
	NOT_ON_TIMER,
	NOT_ON_TIMER,
	NOT_ON_TIMER,
	NOT_ON_TIMER,
	NOT_ON_TIMER,
	NOT_ON_TIMER,
	NOT_ON_TIMER,
	NOT_ON_TIMER,
};

const uint8_t PROGMEM analog_pin_to_channel_PGM[] = {
	7,	// A0				PF7					ADC7
	6,	// A1				PF6					ADC6	
	5,	// A2				PF5					ADC5	
	4,	// A3				PF4					ADC4
	1,	// A4				PF1					ADC1	
	0,	// A5				PF0					ADC0	
	8,	// A6		D4		PD4					ADC8
	10,	// A7		D6		PD7					ADC10
	11,	// A8		D8		PB4					ADC11
	12,	// A9		D9		PB5					ADC12
	13,	// A10		D10		PB6					ADC13
	9	// A11		D12		PD6					ADC9
};

#endif /* ARDUINO_MAIN */
#endif /* Pins_Arduino_h */

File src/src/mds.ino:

#include "Wire.h"
#include "ADXL345.h"
#include "HL1606strip.h"
//#include <SerialCommand.h>

#define VIBRATOR A1     // PC1

#define CHG 3

#define M1 A2
#define M2 A3
#define M3 A6 // ?
#define M4 A7 // ?
#define M5 4
#define M6 7
#define M7 6
#define M8 5

#define REC_PLAY 8
#define LED 2

#define UP(x)   digitalWrite(x, HIGH)
#define DOWN(x) digitalWrite(x, LOW)
#define READ(x) digitalRead(x)

ADXL345 accel;

#define STRIP_D 11
#define STRIP_C 13
#define STRIP_L 10
HL1606strip strip = HL1606strip(STRIP_D, STRIP_L, STRIP_C, 6);

//#define P   Serial.print
//#define PLN Serial.println
//SerialCommand sCmd;

uint8_t Messages[] = {
    M1, M2, M3, M4, M5, M6, M7
};

uint8_t Leds[] = {
    0, 1, 2, 3, 4, 5, 6, 7
};

inline void msgSelect(uint8_t index) {
    DOWN(Messages[index]);
}

inline void msgUnselect() {
    for (char i = 0; i < sizeof(Messages); i++) {
        UP(Messages[i]);
    }
}

inline bool isPlaying() {
    return !READ(LED);
}

bool record(uint8_t index) {
    DOWN(REC_PLAY);
    // Todo: Sleep for 30ns
    DOWN(Messages[index]);
}

bool play(uint8_t index) {
    UP(REC_PLAY);
    // Todo: Sleep for 30ns
    DOWN(Messages[index]);
}

bool stop() {
    msgUnselect();
}

inline void vibrate(int time) {
    UP(VIBRATOR);
    delay(time);
    DOWN(VIBRATOR);
}

inline void ledOff() {
    uint8_t c = 0;
    for (c = 0; c < strip.numLEDs(); c++) {
        strip.setLEDcolor(c, BLACK);
    }

    strip.writeStrip();
}

inline void ledOn(uint8_t index, uint8_t color) {
    strip.setLEDcolor(index, color);
    strip.writeStrip();
}

void setup()
{
    Serial.begin(9600);

    pinMode(VIBRATOR, OUTPUT);
    pinMode(CHG, INPUT);

    pinMode(M1, OUTPUT);
    pinMode(M2, OUTPUT);
    pinMode(M3, OUTPUT);
    pinMode(M4, OUTPUT);
    pinMode(M5, OUTPUT);
    pinMode(M6, OUTPUT);
    pinMode(M7, OUTPUT);

    pinMode(REC_PLAY, OUTPUT);
    pinMode(LED, INPUT);

    DOWN(VIBRATOR);

    msgUnselect();

    UP(REC_PLAY);


    accel.powerOn();

    //accel.setRangeSetting(2);

    accel.setTapThreshold(0x40);
    accel.setTapDuration(0x30);
    accel.setDoubleTapLatency(0x40);
    accel.setDoubleTapWindow(0xFF);
    accel.setTapDetectionOnX(true);
    accel.setTapDetectionOnY(true);
    accel.setTapDetectionOnZ(true);
    accel.setInterrupt(1, true);
    accel.setInterruptMapping(1, true);
 /*
    accel.setAxisOffset(2, 3, 4);
    accel.setActivityThreshold(48);
    accel.setTapDuration(0x30);

    accel.setActivityX(true);
    accel.setActivityY(true);
    accel.setActivityZ(true);
*/

 /*

    colorWipe(RED, 40);
    record(M8);
    delay(3000);
    stop();

    // Setup callbacks for SerialCommand commands
    //sCmd.setDefaultHandler(unrecognized);
    //sCmd.addCommand("accel", cmd_accel);

    colorWipe(YELLOW, 40);
    play(M8);
    delay(3000);
    stop();
*/
}

/*
ISR(TIMER1_OVF_vect)
{
    //TCNT1 = 0;     // reset timer ct to 130 out of 255
    //TCNT1 = 34286;            // preload timer
    TCNT1 = 0;            // preload timer
    //TIFR1 = 0x100;    // timer2 int flag reg: clear timer overflow flag
}
*/

/*
void rainbowParty(uint8_t wait) {
  uint8_t i, j;

  for (i=0; i< strip.numLEDs(); i+=6) {
    // initialize strip with 'rainbow' of colors
    strip.setLEDcolor(i, RED);
    strip.setLEDcolor(i+1, YELLOW);
    strip.setLEDcolor(i+2, GREEN);
    strip.setLEDcolor(i+3, TEAL);
    strip.setLEDcolor(i+4, BLUE);
    strip.setLEDcolor(i+5, VIOLET);

  }
  strip.writeStrip();

  for (j=0; j < strip.numLEDs(); j++) {

    // now set every LED to the *next* LED color (cycling)
    uint8_t savedcolor = strip.getLEDcolor(0);
    for (i=1; i < strip.numLEDs(); i++) {
      strip.setLEDcolor(i-1, strip.getLEDcolor(i));  // move the color back one.
    }
    // cycle the first LED back to the last one
    strip.setLEDcolor(strip.numLEDs()-1, savedcolor);
    strip.writeStrip();
    delay(wait);
  }
}

// have one LED 'chase' around the strip
void chaseSingle(uint8_t color, uint8_t wait) {
  uint8_t i;

  // turn everything off
  for (i=0; i< strip.numLEDs(); i++) {
    strip.setLEDcolor(i, BLACK);
  }

  for (i=0; i < strip.numLEDs(); i++) {
    strip.setLEDcolor(i, color);
    if (i != 0) {
      // make the LED right before this one OFF
      strip.setLEDcolor(i-1, BLACK);
    }
    strip.writeStrip();
    delay(wait);
  }
  // turn off the last LED before leaving
  strip.setLEDcolor(strip.numLEDs() - 1, BLACK);
}

// fill the entire strip, with a delay between each pixel for a 'wipe' effect
void colorWipe(uint8_t color, uint8_t wait) {
  uint8_t i;

  for (i=0; i < strip.numLEDs(); i++) {
      strip.setLEDcolor(i, color);
      strip.writeStrip();
      delay(wait);
  }
}
*/

int getHigher(double data[], int &index, bool &isPlus) {
    int index = 0;
    double largest = abs(data[0]);
    isPlus = (data[0] > 0);
    for (int i = 0; i< 3; i++) {
        if (largest < abs(data[i])) {
            largest = abs(data[i]);
            isPlus = (data[i] > 0);
            index = i;
        }
    }

    return largest;
}

int x, y, z, i;
char data[3];

void loop() {

    bool isPlus = false;
    unsigned int absValue = 0;
    double xyz[3], gains[3], gains_orig[3];

/*
   colorWipe(RED, 40);
   colorWipe(YELLOW, 40);
   colorWipe(GREEN, 40);
   colorWipe(TEAL, 40);
   colorWipe(BLUE, 40);
   colorWipe(VIOLET, 40);
   colorWipe(WHITE, 40);
   colorWipe(BLACK, 40);

   // then a chase
   chaseSingle(RED, 40);
   chaseSingle(YELLOW, 40);
   chaseSingle(GREEN, 40);
   chaseSingle(TEAL, 40);
   chaseSingle(VIOLET, 40);
   chaseSingle(WHITE, 40);

    rainbowParty(60);
*/
/*
    char chg = READ(CHG);
    Serial.write('.');
    Serial.write((int)chg);
*/
    //sCmd.readSerial();
    /*
    delay(5000);
    Serial.write('.');

    return;

    DOWN(VIBRATOR);
    Serial.write("Record");
    record(0);
    delay(5000);
    stop();

    UP(VIBRATOR);
    Serial.write("Play");
    play(0);
    delay(5000);
    stop();

    while(!READ(LED));

    Serial.write("End!");

    delay(5000);
*/

    accel.getInterruptSource();

    if (accel.isActivitySourceOnX()) {
        Serial.print("isActivitySourceOnX(): ");
        Serial.println(accel.isActivitySourceOnX(), DEC);
    }

    if (accel.isActivitySourceOnY()) {
        Serial.print("accel.isActivitySourceOnY(): ");
        Serial.println(accel.isActivitySourceOnY(), DEC);
    }

    if (accel.isActivitySourceOnZ()) {
        Serial.print("accel.isActivitySourceOnZ(): ");
        Serial.println(accel.isActivitySourceOnZ(), DEC);
    }

    if (accel.isTapSourceOnX()) {
        Serial.print("accel.isTapSourceOnX(): ");
        Serial.println(accel.isTapSourceOnX(), DEC);
    }

    if (accel.isTapSourceOnY()) {
        Serial.print("accel.isTapSourceOnY(): ");
        Serial.println(accel.isTapSourceOnY(), DEC);
    }

    if (accel.isTapSourceOnZ()) {
        Serial.print("accel.isTapSourceOnZ(): ");
        Serial.println(accel.isTapSourceOnZ(), DEC);
    }

    //delay(500);

//    memset(&x, 0x00, sizeof(x));
//    memset(&y, 0x00, sizeof(y));
//    memset(&z, 0x00, sizeof(z));

/*
    accel.readAccel(&x, &y, &z);

    Serial.print("XYZ COUNTS: ");
    Serial.print(x, DEC);
    Serial.print(" ");
    Serial.print(y, DEC);
    Serial.print(" ");
    Serial.print(z, DEC);
    Serial.print(".");
*/

    accel.get_Gxyz(xyz);

    Serial.print("XYZ Gs: ");
    for(i = 0; i<3; i++){
        Serial.print(xyz[i], DEC);
        Serial.print(" ");
    }
    Serial.println("");
    //Serial.println(findPositionLargest(xyz, 3), DEC); 

    absValue = getHigher(xyz, index, isPlus);

    // Recording :
    // 1. Lock sur une valeur d'un axe supérieure à 0.7
    // 2. On doit rester sur cette position > 0.7 pendant minimum 1 seconde
    // 3. Accélération sur un axe > 1.6
    // 4. Si tjrs sur le meme axe, on lance le record

    // Record mode
    if (absValue > 1.6) {
        if (!isPlus) {
            index *= 2;
        }

        ledOn(Leds[index], RED);
        vibrate(200);

        record(Messages[index]);

        delay(6000);
        stop();

        vibrate(200);

        stripOff();
    // Play mode
    } else if (absValue > 0.7) {
        
    }
}

/*
void cmd_accel() {
    PLN("Accel");
}

void unrecognized(const char *command) {
    PLN("Command not found !");
}
*/

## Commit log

2013-06-25 Electronique
2013-06-25 First dev
2013-06-27 Schema development
2013-07-01 Schema + PCB
2013-07-08 Modif PCB - rev 0.5.1
2013-07-18 PCB Version 0.6.2
2013-08-01 Source code
2013-08-04 Code + Doc + OpenScad
2013-08-05 OpenScad work
2013-08-05 OpenScad works
2013-08-07 Parabole (OpenScad)
2013-08-07 Code
2013-08-08 Modif
2013-08-24 Code !
2013-08-29 Code + Cad
2013-09-02 PCB : Bluetooth module + enhancement
2013-09-04 Stl file + PCB
2013-09-11 PCB 0.8.0
2013-09-30 SCad, Texture
2013-10-01 Texture + Code hardware 0.8.0
2013-10-02 Bump mapping
2013-10-07 Clean, code, openscad
2013-10-09 Cad, export
2013-10-13 Code, Cad
2013-10-14 Museolab
2013-10-24 Page creation
2013-10-24 NeoPixel adaptation
2013-10-30 Update !
2013-11-06 Message
    - MAX_BRIGHTNESS
    - Welcome message
    - Charged message
2013-11-19 Power control
2013-11-19 Modif schéma
2014-03-25 Debug + WatchDog
2016-04-19 Documentation
2016-04-19 Source update
2016-04-19 Update CAD
2016-04-19 New version 2 in progress
2016-05-07 VS1053B Datasheet
2016-05-07 Work on Schematic / PCB
2016-07-04 Add som datasheet
2016-07-04 Add 2.0.0 PCB gerber files
2016-07-04 Remove 0.8.0 gerber archive
2016-07-04 Add PCB 2.0.0
2016-07-04 Remove useless drivers
2016-07-04 Add new drivers
    * VS1053 (Ogg Vorbis/MP3/AAC/WMA/FLAC/ MIDI audio code circuit)
    * LSM303 (Ultra compact high performance e-compass 3D accelerometer and
    3D magnetometer module)
    * MCP79410 (Battery-Backed I2CTM Real-Time Clock/Calendar with SRAM,
    EEPROM and Protected EEPROM)
2016-07-05 Add SD/FAT drivers
2016-07-05 Add boards.txt with MurmureDuSon 2 config
    You have to append your own boards.txt with this.
2016-07-05 Add MurmureDuSon 2 variant
    Add this in your Arduino variants path
2016-07-05 Disable TXLED / RXLED
    TXLED and RXLED are used to driver VS1053
2016-07-05 Patch SD driver to use TXLED as SD chip select
2016-07-05 Patch VS1053 driver to use RXLED as SPI chip select

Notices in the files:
parts and their libraries:
SparkFun-Sensors: Licensing: CC v3.0 Share-Alike You are welcome to use this library for commercial purposes.
microbuilder: This work is placed in the public domain, and may be freely used for commercial and non-commercial work with the following conditions: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
